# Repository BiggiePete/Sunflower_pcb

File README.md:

# Sunflower_pcb
Sunflower is a simple pcb board to control a opening and closing solar panel

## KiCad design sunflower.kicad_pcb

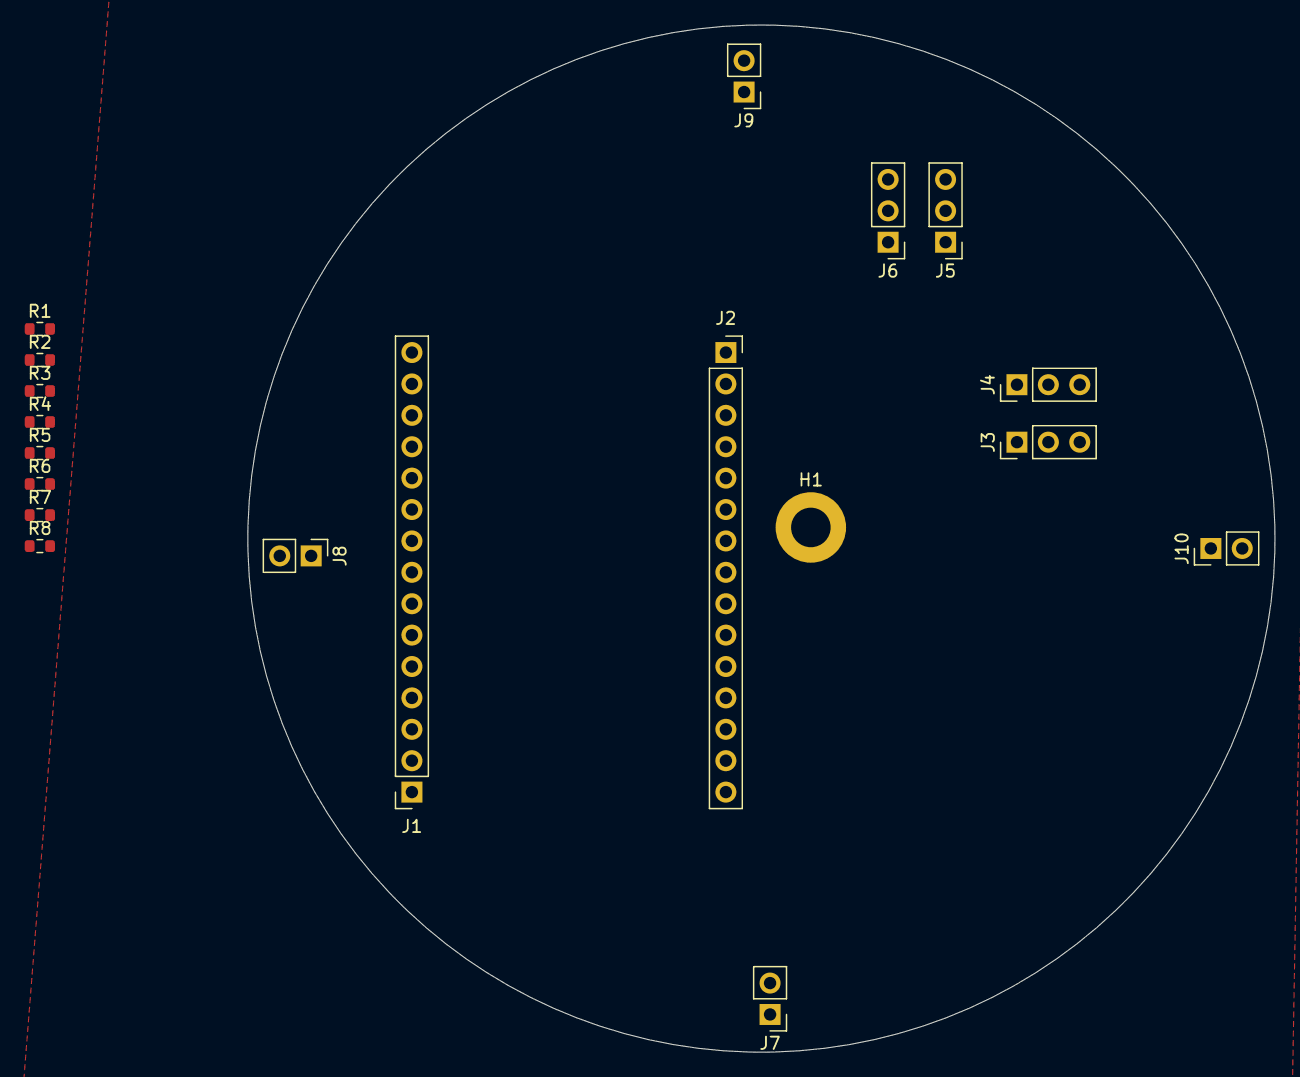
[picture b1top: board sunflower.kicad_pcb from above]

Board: 2 copper layers, 83.1 x 83.1 mm, 19 parts (0 on the bottom side), 16 nets, no tracks yet.

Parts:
H1: MountingHole_Pad; MountingHole_3.2mm_M3_ISO7380_Pad
J1, J2: Conn_01x15_Socket; PinSocket_1x15_P2.54mm_Vertical
J3, J4, J5, J6: Conn_01x03_Pin; PinHeader_1x03_P2.54mm_Vertical
J7, J8, J9, J10: Conn_01x02_Pin; PinHeader_1x02_P2.54mm_Vertical
R1, R2, R3, R5, R7, R8: 10K; R_0603_1608Metric
R4: 20K; R_0603_1608Metric
R6: 1K; R_0603_1608Metric

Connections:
+5V: J1.15, J3.2, J4.2, J5.2, J6.2
/BAT_EN_READ: J2.7, R1.1
/BAT_READ: J1.10, R3.2, R4.1
/D2/Sense180deg: J2.4, J9.1
/D12/Sense0deg: J1.12, J7.1
/D13/Sense90deg: J1.13, J8.1
/D15/Sense270deg: J2.3, J10.1
/D25/S3: J1.8, J5.1
/D26/S4: J1.9, J6.1
/D34/S1: J1.4, J3.1
/D35/S2: J1.5, J4.1
/PANEL_EN_READ: J2.6, R5.1
/PANEL_READ: J1.11, R6.2, R7.1
GND: H1.1, J1.14, J2.2, J3.3, J4.3, J5.3, J6.3, J7.2, J8.2, J9.2, J10.2, R1.2, R3.1, R5.2, R6.1
unnamed: R2.1, R4.2
unnamed: R7.2, R8.1

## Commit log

2025-03-16 begin
